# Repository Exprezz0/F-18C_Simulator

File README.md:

# F/A-18C Simulator Cockpit
Based on OpenHornet design (https://www.OpenHornet.com) - Modified for Personal Use.  

# Disclaimer
The files located within this repository have been created from scratch or modified from existing OpenHornet files and were adapated to suit my personal needs based on available resources.   There may or may not be easier or more efficient ways to produce some of the systems/designs here, but for the purpose of learning and gaining knowledge and experience designing, engineering, manufacturing, resourcing, etc., I've decided to take the more difficult path.

1:  Any modification, usage, sharing, distribution, etc falls under the same licenses and legal definitions that apply to OpenHornet.

2:  It is not 100% complete.  I will add to it as I continue to progress my own pit.

3:  Use at your own risk.  The files within the repo may or may not be up to date with the current OH design.  I've already cut, printed, and engraved most of the project and have modified various files to fit my own personal needs and resources.

4:  I've done my best to keep it organized.  If you see something out of place (meaning: incorrect directory, not missing.  See #2), please PM me and I'll fix it.

5:  Most importantly, while the files are 94.271% OpenHornet, there are modifications in there.  Please do not reference any files taken from my repository in the OpenHornet Discord.  It's not the developers, contributors, or testers responsibility to answer questions or fix issues associated with 3rd party files.  I'll be more than happy to answer questions offline, and if it relates directly to OpenHornet, we can bring up the issue here.

# File Structure

**This repository has been organized in the following manner:**

The MCAD folder contains all .STL, .SVG, .DXF files types for all mechanical manufacturing.  Within the MCAD folder are the 5 Major Assesmbly Groups: 

```c
* MCAD
     * ASSY, UPPER INSTRUMENT PANEL
     * ASSY, LOWER INSTRUMENT PANEL
     * ASSY, CENTER TUB
     * ASSY, LEFT CONSOLE
     * ASSY, RIGHT CONSOLE
```

 Sub-assemblies for each major group will be broken down into their own individual folders.  Files organic to that sub-assembly will be located in one of several child folders based on the material they are comprised of.  (Resin, PETG, MDF, Acrylic).
    
Additionally, each major assembly will also have:
   1. "**ALL PANEL PLATES**" folder; includes the *Backlight Plate, Light Plate*, and *Legend Plate* folders associated with that major assembly

   2. "**ALL KNOBS**" folder; includes all knobs associated with that major assembly.

   3. "**RANDOM COTS PARTS**" folder; includes any COTS that could be resin printed or manufactured without having to order or purchase.  Examples include gears, bearings, spacers....

   4. "**OBSOLETE**" folder; contains files that are outdated or no longer belong to the OH project.

    * ASSY, RIGHT CONSOLE
        * ALL PANEL PLATES
        * ALL KNOBS
        * OBSOLETE
        * RANDOM COTS PARTS
        * OH5A2A2-1 - ASSY, WING FOLD HANDLE
        * OH5A2A1-1 - ASSY, HOOK LEVER & INDICATOR
        * OH5A1A1-1 - ASSY, RIGHT CONSOLE STRUCTURE
            * ACRYLIC
            * MDF
            * PETG
         
Lastly, each material folder will be broken down into size for reference.  If a part/object is suppose to be printed in PETG or ABS, and you can't find it, try looking in another material folder.  Sometimes I prefered resin printing or using acrylic to the defaulted PETG.

# ECAD Directory

The ECAD folder is set up similar to the MCAD directory (in this repository, and almost as identical to the official OpenHornet repository) and navigating it should be just as easy.  

As of right now, all of the backlit panels have been transitioned to KiCad 6, the libraries associated with the files are consolidated and reorganized, and new manufacturing files that includes TOP and BOTTOM Bill of Materials (BOM) have been created to facilitate easier ordering from JLCPCB.com.

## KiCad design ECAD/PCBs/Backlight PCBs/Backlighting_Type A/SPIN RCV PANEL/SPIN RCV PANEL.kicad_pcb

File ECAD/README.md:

* [OpenHornet Website](https://www.openhornet.com)
* [OpenHornet Discord](https://discord.gg/G5PA5ju)
* [Donate to OpenHornet](https://www.openhornet.com/campaigns/donate/)

# **ECAD DIRECTORY INFORMATION**

The purpose of this guide is to help enable the end-user to successfully accomplish the following:  
*   1:  Facilitate navigation of the file structure.
*   2:  Provide clarification regarding the manufacturing process of PCB's related to OpenHornet using JLCPCB.com
*   2:  How to install KiCad 6 and set up libraries associated with OpenHornet. _(optional)__

 _Note:  Manufacturing files have been generated accordinging to JLCPCB.com guidelines.  If choosing a different PCB Manufacturer, make sure to research their formatting standards and modify the necessary manufacturing files accordingly. And if you choose to manufacture them yourself, best of luck!_

## **ECAD File Structure**

The ECAD Directory has been organized to facilitate the end user, regardless of skill or knowledge, in acquiring the necessary files needed to: 
* A: make adjustments to individual PCB's as needed using ECAD software (KiCad)
     * _and/or_
* B: submit an online order to have the PCB manufactured and assembled by a company.

**The structure of the ECAD Directory is summarized below:**

1. Within each labeled PCB folder, there will be a folder called "JLCPCB" and inside of that folder will be two additional folders called "gerbers" and "production_files"
2. **_All files you need for manufacturing are located in the "production_files" folder.  The gerbers are already compressed in a .zip file labeled the same way as the PCB folder their located in._** 
3. Additionally, there will be 3 .csv files:  _**BOM_BOTTOM-'NAME OF PANEL'.csv**_,  _**BOM_TOP-'NAME OF PANEL'.csv**_, AND  _**CPL-'NAME OF PANEL'.csv**_ that will contain a Bill of Materials for both components located on both the top and bottom of the PCB, as well as the CPL used for placing the components.

***PLEASE READ:  YOU NEED TO DOWNLOAD ALL 4 FILES WITHIN THE PRODUCTION_FILES FOLDER.  NOT JUST THE .ZIP.***

## **PCB Manufacturing**

At the moment, all manufacturing files have been standardized to allow for fabrication using JLC @ (https://www.jlcpcb.com).  You may use another PCB manufacturer of your choosing; however, you will be responsible for ensuring the required files meet specifications and formatting. 

***For details on the JLCPCB manufacturing process, please see the "MANUFACTURING.MD" located in the ECAD folder or CLICK THE LINK BELOW***

  [JLCPCB MANUFACTURING PROCESS & FAQ](MANUFACTURING.MD)

## **Installation of KiCad and OpenHornet Libraries _(OPTIONAL)_**

*Installation of KiCad and OpenHornet Libraries is only required if you choose to contribute.  See [CONTRIBUTING.MD](https://github.com/jrsteensen/OpenHornet/blob/v1.0.0-beta1/CONTRIBUTING.md) for more details.*

Before we begin, it is assumed that you have:
*  1:  Downloaded the latest version of KiCad _(currently KiCad 6.0.9)_ and installed it on your computer.  
*  2:  Cloned the OpenHornet repository

#### STEP ONE:  Configure Paths & Create Environmental Variables
Open up a new or previous project in KiCad.  For this example, I'll be using the MASTER ARM PANEL.  In the Top Menu: Navigate to Preferences --> Configure Paths

Create 4 new variables with the following Names and paths:
*  1:  KICAD6_USER_OH_3DMODELS
*  2:  KICAD6_USER_OH_FOOTPRINTS
*  3:  KICAD6_USER_OH_SYMBOLS
*  4:  KICAD6_USER_OH_TEMPLATES

The paths can be anywhere so long as it points to your Open Hornet directory.  _Make sure the OH_FOOTPRINTS variable points to the \ECAD\lib folder and **NOT** \ECAD\lib\OH_FOOTPRINTS.PRETTY_.

#### STEP TWO:  Add OpenHornet Symbol and Footprint Libraries

With the project window open, navigate to Preferences --> Manage Symbol Libraries.

When the Symbol Libraries window opens, make sure you are in the **"Global Libraries"** tab and then check the bottom for a section called "Path Substitutions".  Ensure that the environmental variable that you just created is located in there.  _If you're using a previous version of KiCad or have older libraries still installed, click "Migrate Libraries" after selecting them to transition them to KiCad 6.  The library format will say "Legacy" if its outdated, and "KiCad" if it's compatible. If you have a fresh install, you can skip this step._

Next, click on the folder icon near the bottom left and navigate to  _\ECAD\lib\OH_Symbols_ and add the four kicad_sym files located in the folder.  This will automatically populate the fields with the information.  Alternatively, you click on the "+" icon to add a new row and manually enter the information for your libraries.  

Finally, check the Library Path to make sure your environmental variable was adopted.

Do the same thing for the footprint Libraries:

#### STEP THREE:  Add ***KiCAD JLCPCB tools*** Plugin (Optional)
Bouni @ https://github.com/bouni/kicad-jlcpcb-tools has developed a great plugin that allows you to search the JLCPCB parts database, assign LCSC article numbers to your parts, and generate production files for JLCPCB.

*  1: Click **"Plugin and Content Manager"**
*  2: When the dialog box opens, click on **"Manage"**
*  3: When the **"Manage Repositories"** dialog box opens, Click the "+" sign and add the following:
    *  Name:  Bouni's KiCad repository
    *  URL:  https://raw.githubusercontent.com/Bouni/bouni-kicad-repository/main/repository.json
*  4: Once downloaded and installed, hit "Apply Changes"

### Congratulations. That's all you have to do.  The 3D models that are associated with the footprints will automatically be linked as long as the OH_Footprints are used.

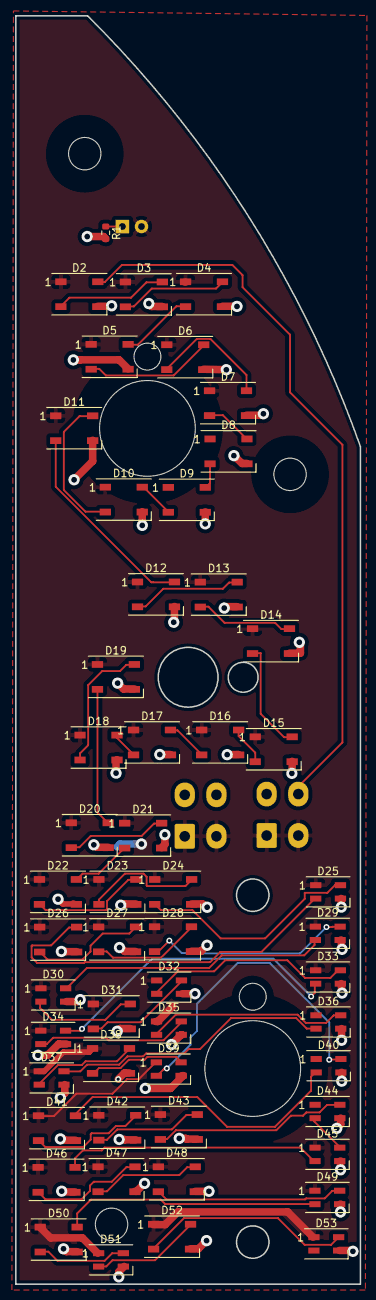
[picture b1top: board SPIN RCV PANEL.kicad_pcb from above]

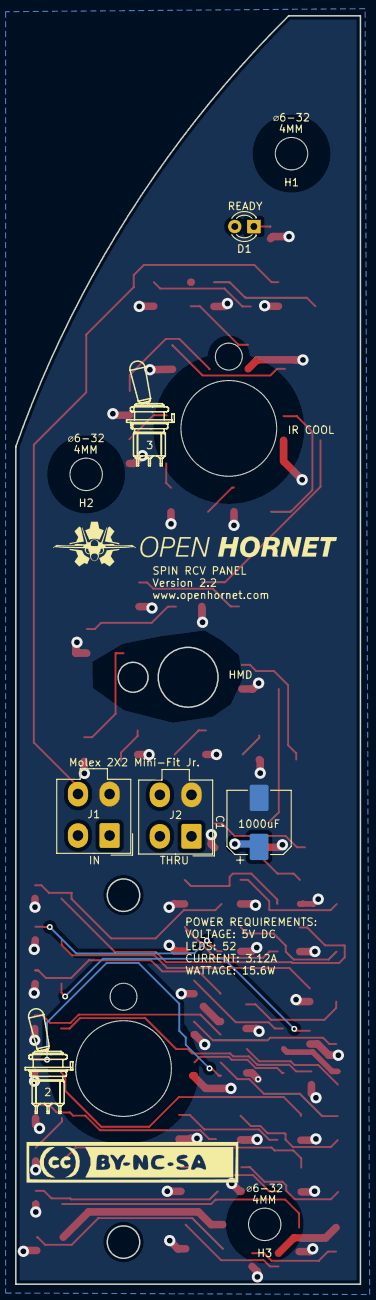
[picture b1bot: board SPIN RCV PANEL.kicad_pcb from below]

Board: 2 copper layers, 45.7 x 168.3 mm, 58 parts (4 on the bottom side), 55 nets.

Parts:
C1: C_Polarized; CP_Elec_8x10
D1: LED; LED_D3.0mm
D2, D3, D4, D5, D6, D7, D8, D9, D10, D11, D12, D13, D14, D15, D16, D17, D18, D19, D20, D21, D22, D23, D24, D26, D27, D28, D31, D38, D41, D42, D43, D46, D47, D48, D50, D52: WS2812B; LED_WS2812B_PLCC4_5.0x5.0mm_P3.2mm
D25, D29, D30, D32, D33, D34, D35, D36, D37, D39, D40, D44, D45, D49, D51, D53: WS2812B; LED_WS2812B-MINI_PLCC4_3.5x3.5mm_P1.75mm
G1: LOGO; 100SpxToggle
J1, J2: Conn_01x04_Female; Molex_Mini-Fit_Jr_5566-04A_2x02_P4.20mm_Vertical
R1: R; R_0603_1608Metric

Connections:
/DATAIN: D2.4, J1.4
/LED+5V: C1.1, D1.2, D2.1, D3.1, D4.1, D5.1, D6.1, D7.1, D8.1, D9.1, D10.1, D11.1, D12.1, D13.1, D14.1, D15.1, D16.1, D17.1, D18.1, D19.1, D20.1, D21.1, D22.1, D23.1, D24.1, D25.1, D26.1, D27.1, D28.1, D29.1, D30.1, D31.1, D32.1, D33.1, D34.1, D35.1, D36.1, D37.1, D38.1, D39.1, D40.1, D41.1, D42.1, D43.1, D44.1, D45.1, D46.1, D47.1, D48.1, D49.1, D50.1, D51.1, D52.1, D53.1, J1.1, J1.2, J2.1, J2.2
/LEDGND: C1.2, D2.3, D3.3, D4.3, D5.3, D6.3, D7.3, D8.3, D9.3, D10.3, D11.3, D12.3, D13.3, D14.3, D15.3, D16.3, D17.3, D18.3, D19.3, D20.3, D21.3, D22.3, D23.3, D24.3, D25.3, D26.3, D27.3, D28.3, D29.3, D30.3, D31.3, D32.3, D33.3, D34.3, D35.3, D36.3, D37.3, D38.3, D39.3, D40.3, D41.3, D42.3, D43.3, D44.3, D45.3, D46.3, D47.3, D48.3, D49.3, D50.3, D51.3, D52.3, D53.3, J1.3, J2.3, R1.2
unnamed: D1.1, R1.1
unnamed: D2.2, D3.4
unnamed: D3.2, D4.4
unnamed: D4.2, D5.4
unnamed: D5.2, D6.4
unnamed: D6.2, D7.4
unnamed: D7.2, D8.4
unnamed: D8.2, D9.4
unnamed: D10.2, D11.4
unnamed: D9.2, D10.4
unnamed: D11.2, D12.4
unnamed: D12.2, D13.4
unnamed: D13.2, D14.4
unnamed: D14.2, D15.4
unnamed: D15.2, D16.4
unnamed: D16.2, D17.4
unnamed: D17.2, D18.4
unnamed: D18.2, D19.4
unnamed: D19.2, D20.4
unnamed: D20.2, D21.4
unnamed: D21.2, D22.4
unnamed: D22.2, D23.4
unnamed: D23.2, D24.4
unnamed: D24.2, D25.4
unnamed: D25.2, D26.4
unnamed: D26.2, D27.4
unnamed: D27.2, D28.4
unnamed: D28.2, D29.4
unnamed: D29.2, D30.4
unnamed: D30.2, D31.4
unnamed: D31.2, D32.4
unnamed: D32.2, D33.4
unnamed: D33.2, D34.4
unnamed: D34.2, D35.4
unnamed: D35.2, D36.4
unnamed: D36.2, D37.4
unnamed: D37.2, D38.4
unnamed: D38.2, D39.4
unnamed: D39.2, D40.4
unnamed: D40.2, D41.4
unnamed: D41.2, D42.4
unnamed: D42.2, D43.4
unnamed: D43.2, D44.4
unnamed: D44.2, D45.4
unnamed: D45.2, D46.4
unnamed: D46.2, D47.4
unnamed: D47.2, D48.4
unnamed: D48.2, D49.4
unnamed: D49.2, D50.4
unnamed: D50.2, D51.4
unnamed: D51.2, D52.4
unnamed: D52.2, D53.4

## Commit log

2023-01-02 Initial Commit - Left Console
    First commit of the Left Console Assembly: It is not complete in terms of everything needed for OpenHornet. It contains the files that I've modified and/or exported to be cut, printed, lased, etc.
    1: The majority of the left console is there, however, there may be parts missing from the OH repository.
    2: Some of the parts may be outdated or from previous versions of assemblies with OpenHornet that I've already printed out and am currently using.
2023-01-02 Initial Upload - Remaining OH Simplit files
    Remaining files not including the Left Console Assembly.
    +ECAD
    +Additional Resources
2023-01-02 ReadMe.md Update
2023-01-02 LC Knobs Update
    Added 3 Knobs:
    1: Transducer Gain Knob
    2: SIM PWR PANEL, BKLT Mode Knob
    3: EXT LIGHT PANEL, Formation & Position Lights Knob.
    Fixed naming convention of knobs to keep it organized.
2023-01-02 Final LC Knobs Added
    Added 2x Pushbutton Caps for switches on the Landing Gear Panel. This should complete the required knobs for the Left Console for the moment.
2023-01-02 Create LICENSE.md
    Added OpenHornet License
2023-01-02 ECS PANEL Knobs Added
2023-01-03 WinWing Throttle Modifcation
    Added "WINWING Throttle Mod" folder under "Left Console Structure". Any modifications to the structure, regardless of material type, will be placed here as it pertains to the Winwing throttle.
2023-01-03 RC Knobs and Panels update
    1:) Added - Dual concentric Pot assembly (used in 2 panels on the right side. Parts for assembly are split between the COTS folder and Assembly folder titled ASSY, DUAL CONCENTRIC SHAF POTENTIOMETER.
    2:) Added - Defog lever and a few more knobs needed on the right console.
    3:) Added - Inboard Wall support for Left Console. Used in the front right corner of the Left Console on the floor to help attach left inboard wall.
2023-01-04 Added: L/R Console Legend Panels for engraving
    Added .stl and .svg's for various panels
2023-01-06 PCB Renaming
    Since the name of the projects included "PCB, [NAME PANEL]", anytime manufacturing files or anything were created, it named all of the file within the project the same. This includes the BOM and CPL 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
    Also, having "PCB" included in the name of the PCB, under a folder called "PCBs" with in the Electrical CAD folder, seemed kind of ..... redundant.
    Looks cleaner and easier to navigate by removing PCB from the front. Each project is being saved as a new project with a new name, which automatically changes the name of each file within its subdire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
2023-01-06 ECM-DISP CPL File Update.
2023-01-06 Manufacturing File Update
    APU
    ANT SEL
2023-01-06 Manufacturing File Update
    CAUTION LIGHTS PANEL
    AV COOL PANEL
2023-01-07 Manufacturing File Update #3
    COMM
    DEFOG
    ECM DISP
    ECS
    ELEC
    EXT LT
2023-01-07 Manufacturing File Update #3
    HUD VID RCD
    HYD ISO
    INTR LT
    JETT STATION SELECT PLACARD
    KY-58
    LANDING GEAR PANEL
2023-01-07 Manufacturing File Update #4
    OBOGS
    SELECT JETT
    SIM CONTROL
    SIM POWER
    SNSR
    SPIN RCV
2023-01-09 Knob/Panel Update
    Added: A few more Right Console Knobs
    Removed: Duplicate Panel Lightburn files from left console
2023-01-10 ECAD Directory update.
2023-01-12 Right Console Panels
    Remaining Right Console Panels added
2023-01-13 Right Console Panel/Knob Update
    Added INS/RDR Knobs
    Added modified Panels
2023-01-14 Panel Update
2023-01-14 Create OH4A6A1-11 - FCS PANEL BACKPLATE_ver2, .50in RudTrim.svg
    Modifed FCS Backplate to fit different Rud Trim assembly.
2023-01-14 PDU Removal
    ABSIS_PDU was replaced by ABSIS_ATX_PSU
2023-02-01 Manufacturing.MD update.
2023-02-06 Read Me update
2023-02-07 Update README.md
    Added JLCPCB plugin section
2023-02-10 Huge ECAD push
2023-03-08 Software Test
2023-03-08 Software update
2023-03-20 Test (broken code)
    Used for reference to fix new script
2023-03-26 Software Test
    Dont use, test for platformIO
2023-04-01 software update
    Use of Arduino IDE and Platform IO. Adjusted file structure to match.
2023-04-02 Added BATT VOLT INDICATOR
2023-04-22 Reorganized/Added Panel Plates
2023-04-25 Added Bleed Air Assembly to MCAD
